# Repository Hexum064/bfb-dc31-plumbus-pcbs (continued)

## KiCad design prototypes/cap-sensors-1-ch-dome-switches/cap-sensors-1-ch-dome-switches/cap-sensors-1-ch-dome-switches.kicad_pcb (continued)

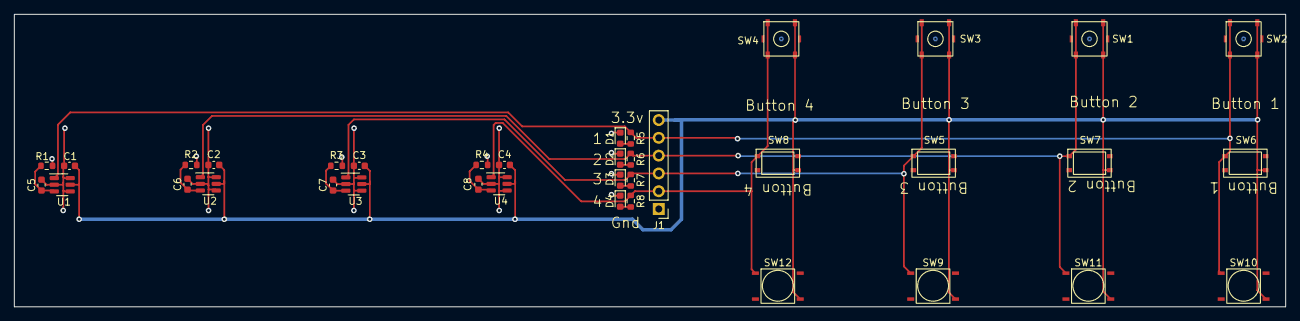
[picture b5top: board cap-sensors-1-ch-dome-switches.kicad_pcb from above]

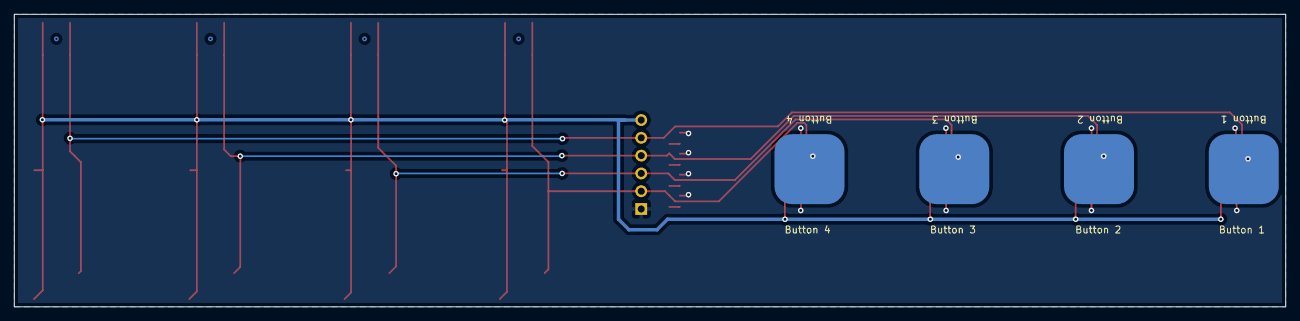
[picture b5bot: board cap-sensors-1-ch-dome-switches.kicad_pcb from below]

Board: 2 copper layers, 181.5 x 41.8 mm, 41 parts (4 on the bottom side), 18 nets.

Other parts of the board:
Button 1, Button 2, Button 3, Button 4: TP; touch_pad

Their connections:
unnamed 14: Button 1.1 (Touch_Pad); also elsewhere on the board
unnamed 15: Button 2.1 (Touch_Pad); also elsewhere on the board
unnamed 16: Button 3.1 (Touch_Pad); also elsewhere on the board
unnamed 17: Button 4.1 (Touch_Pad); also elsewhere on the board

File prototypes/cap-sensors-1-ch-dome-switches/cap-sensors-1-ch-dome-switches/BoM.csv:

Designator,Comment,Footprint,JLCPCB Part #
"C1, C2, C3, C4",100nF,Capacitor_SMD:C_0603_1608Metric,
"C5, C6, C7, C8",1pF,Capacitor_SMD:C_0603_1608Metric,
"D1, D2, D3, D4",LED,LED_SMD:LED_0603_1608Metric,
J1,Conn_01x06_Female,Connector_PinHeader_2.54mm:PinHeader_1x06_P2.54mm_Vertical,C2833331
"R1, R2, R3, R4, R5, R6, R7, R8",1K,Resistor_SMD:R_0603_1608Metric,
"SW1,SW2,SW3,SW4",Tactile Switch,dome_buttons:EVQPLDA15,C424352
"SW5,SW6,SW7",Tactile Switch,dome_buttons:GT-TC170B-H0078-L10,C2896623
"SW9,SW10,SW11,SW12",Tactile Switch,dome_buttons:TS5208A,C557590
"U1,U2,U3,U4",RH6015-C,RH6015-C,C78180

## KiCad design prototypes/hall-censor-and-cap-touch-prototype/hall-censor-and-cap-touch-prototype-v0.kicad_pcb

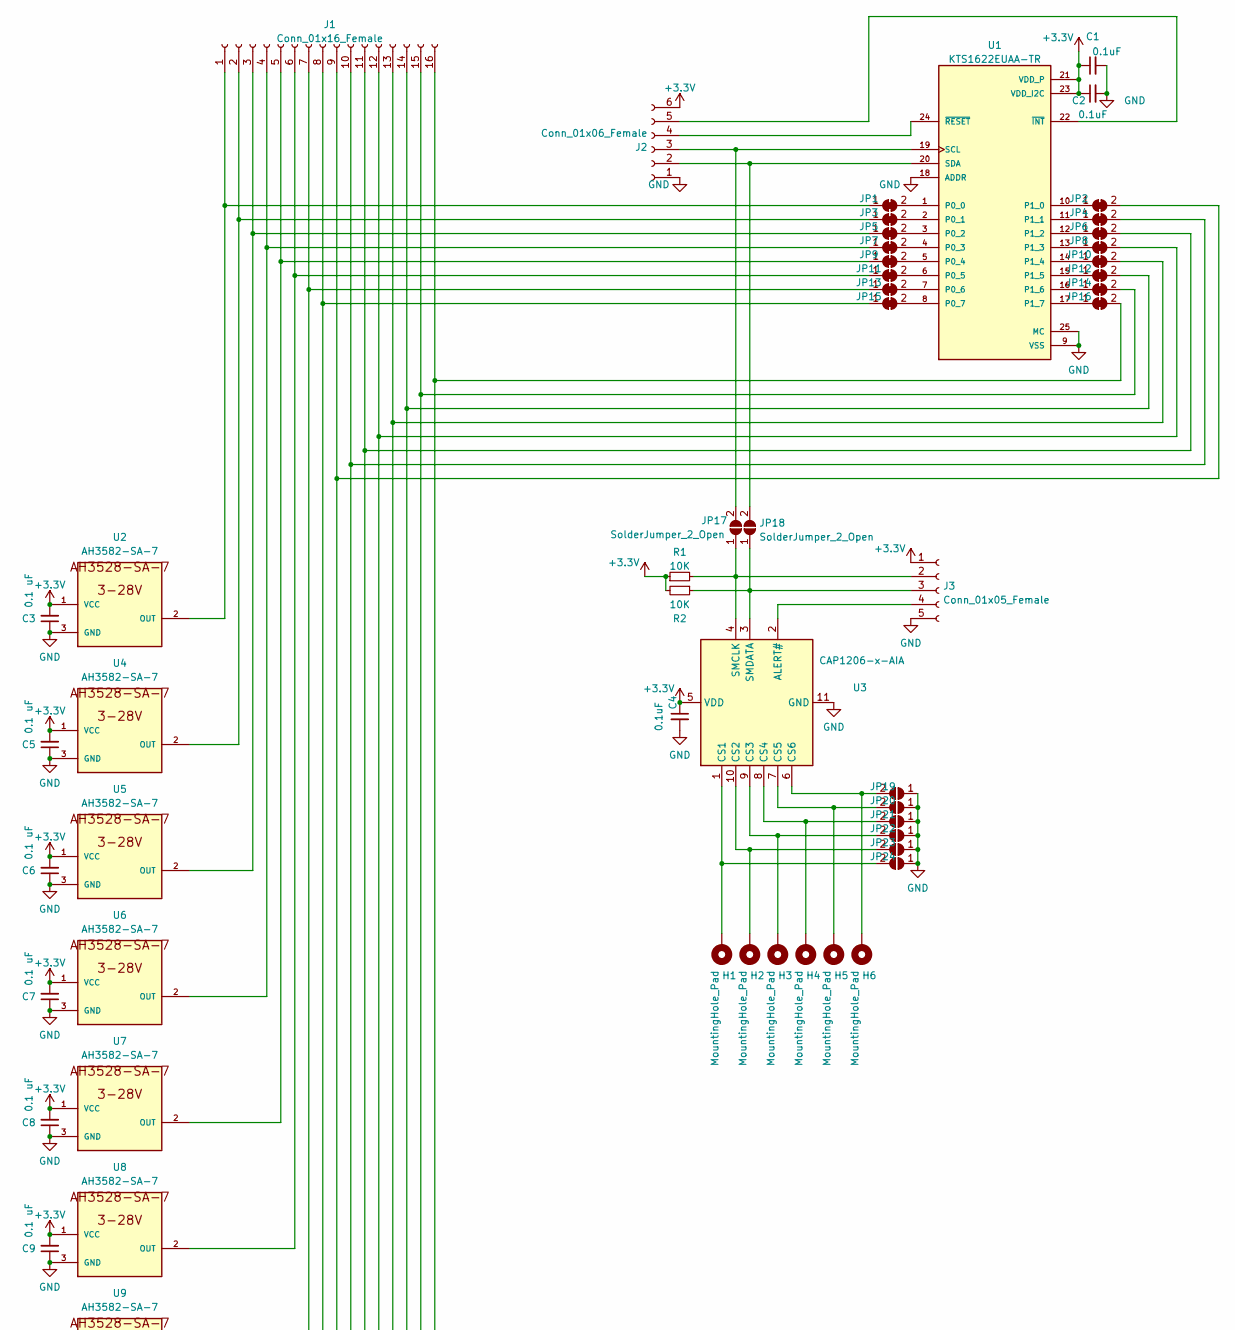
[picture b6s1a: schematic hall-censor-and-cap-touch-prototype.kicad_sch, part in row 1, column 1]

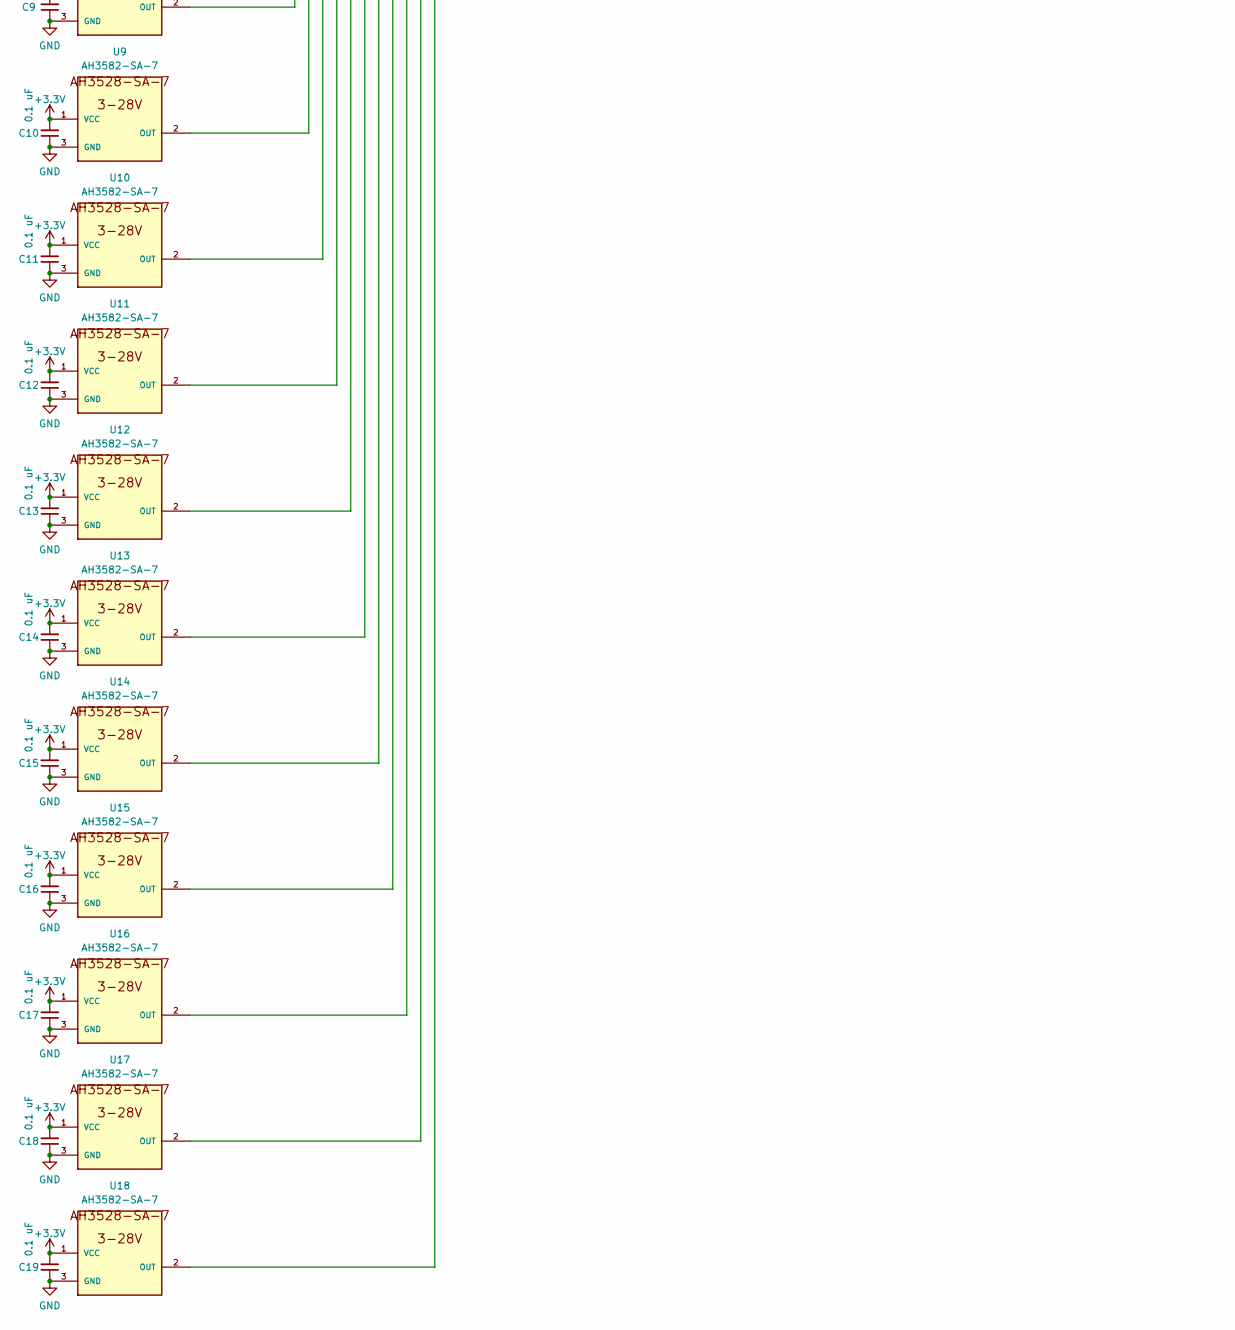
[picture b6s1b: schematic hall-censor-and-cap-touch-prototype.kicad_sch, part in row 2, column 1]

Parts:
C1, C2, C4: 0.1uF; C_0603_1608Metric
C3, C5, C6, C7, C8, C9, C10, C11, C12, C13, C14, C15, C16, C17, C18, C19: 0.1 uF; C_0603_1608Metric
H1, H2, H3, H4, H5, H6: MountingHole_Pad; TestPoint_Pad_4.0x4.0mm
J1: Conn_01x16_Female; PinHeader_1x16_P2.54mm_Vertical
J2: Conn_01x06_Female; PinHeader_1x06_P2.54mm_Vertical
J3: Conn_01x05_Female; PinHeader_1x05_P2.54mm_Vertical
JP1, JP2, JP3, JP4, JP5, JP6, JP7, JP8, JP9, JP10, JP11, JP12, JP13, JP14, JP15, JP16: SolderJumper_2_Bridged; SolderJumper-2_P1.3mm_Bridged2Bar_RoundedPad1.0x1.5mm
JP17, JP18, JP19, JP20, JP21, JP22, JP23, JP24: SolderJumper_2_Open; SolderJumper-2_P1.3mm_Open_RoundedPad1.0x1.5mm
R1, R2: 10K; R_0603_1608Metric
U1: KTS1622EUAA-TR; QFN50P400X400X80-25N; PARTREV 04d
U2, U4, U5, U6, U7, U8, U9, U10, U11, U12, U13, U14, U15, U16, U17, U18: AH3582-SA-7; SOT-23-AH3582-SA-7
U3: CAP1206-x-AIA; DFN-10-1EP_3x3mm_P0.5mm_EP1.55x2.48mm

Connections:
+3V3: C1.1, C2.1, C3.2, C4.1, C5.2, C6.2, C7.2, C8.2, C9.2, C10.2, C11.2, C12.2, C13.2, C14.2, C15.2, C16.2, C17.2, C18.2, C19.2, J2.6, J3.1, R1.1, R2.2, U1.21 (VDD_P), U1.23 (VDD_I2C), U2.1 (VCC), U3.5 (VDD), U4.1 (VCC), U5.1 (VCC), U6.1 (VCC), U7.1 (VCC), U8.1 (VCC), U9.1 (VCC), U10.1 (VCC), U11.1 (VCC), U12.1 (VCC), U13.1 (VCC), U14.1 (VCC), U15.1 (VCC), U16.1 (VCC), U17.1 (VCC), U18.1 (VCC)
GND: C1.2, C2.2, C3.1, C4.2, C5.1, C6.1, C7.1, C8.1, C9.1, C10.1, C11.1, C12.1, C13.1, C14.1, C15.1, C16.1, C17.1, C18.1, C19.1, J2.1, J3.5, JP19.1 (A), JP20.1 (A), JP21.1 (A), JP22.1 (A), JP23.1 (A), JP24.1 (A), U1.9 (VSS), U1.18 (ADDR), U1.25 (MC), U2.3 (GND), U3.11 (GND), U4.3 (GND), U5.3 (GND), U6.3 (GND), U7.3 (GND), U8.3 (GND), U9.3 (GND), U10.3 (GND), U11.3 (GND), U12.3 (GND), U13.3 (GND), U14.3 (GND), U15.3 (GND), U16.3 (GND), U17.3 (GND), U18.3 (GND)
unnamed: H1.1, JP24.2 (B), U3.1 (CS1)
unnamed: H2.1, JP23.2 (B), U3.10 (CS2)
unnamed: H3.1, JP22.2 (B), U3.9 (CS3)
unnamed: H4.1, JP21.2 (B), U3.8 (CS4)
unnamed: H5.1, JP20.2 (B), U3.7 (CS5)
unnamed: H6.1, JP19.2 (B), U3.6 (CS6)
unnamed: J1.1, JP1.1 (A), U2.2 (OUT)
unnamed: J1.2, JP3.1 (A), U4.2 (OUT)
unnamed: J1.3, JP5.1 (A), U5.2 (OUT)
unnamed: J1.4, JP7.1 (A), U6.2 (OUT)
unnamed: J1.5, JP9.1 (A), U7.2 (OUT)
unnamed: J1.6, JP11.1 (A), U8.2 (OUT)
unnamed: J1.7, JP13.1 (A), U9.2 (OUT)
unnamed: J1.8, JP15.1 (A), U10.2 (OUT)
unnamed: J1.9, JP2.2 (B), U11.2 (OUT)
unnamed: J1.10, JP4.2 (B), U12.2 (OUT)
unnamed: J1.11, JP6.2 (B), U13.2 (OUT)
unnamed: J1.12, JP8.2 (B), U14.2 (OUT)
unnamed: J1.13, JP10.2 (B), U15.2 (OUT)
unnamed: J1.14, JP12.2 (B), U16.2 (OUT)
unnamed: J1.15, JP14.2 (B), U17.2 (OUT)
unnamed: J1.16, JP16.2 (B), U18.2 (OUT)
unnamed: J2.2, JP18.2 (B), U1.20 (SDA)
unnamed: J2.3, JP17.2 (B), U1.19 (SCL)
unnamed: J2.4, U1.24 (~RESET)
unnamed: J2.5, U1.22 (~INT)
unnamed: J3.2, JP17.1 (A), R1.2, U3.4 (SMCLK)
unnamed: J3.3, JP18.1 (A), R2.1, U3.3 (SMDATA)
unnamed: J3.4, U3.2 (ALERT#)
unnamed: JP1.2 (B), U1.1 (P0_0)
unnamed: JP2.1 (A), U1.10 (P1_0)
unnamed: JP3.2 (B), U1.2 (P0_1)
unnamed: JP4.1 (A), U1.11 (P1_1)
unnamed: JP5.2 (B), U1.3 (P0_2)
unnamed: JP6.1 (A), U1.12 (P1_2)
unnamed: JP7.2 (B), U1.4 (P0_3)
unnamed: JP8.1 (A), U1.13 (P1_3)
unnamed: JP9.2 (B), U1.5 (P0_4)
unnamed: JP10.1 (A), U1.14 (P1_4)
unnamed: JP11.2 (B), U1.6 (P0_5)
unnamed: JP12.1 (A), U1.15 (P1_5)
unnamed: JP13.2 (B), U1.7 (P0_6)
unnamed: JP14.1 (A), U1.16 (P1_6)
unnamed: JP15.2 (B), U1.8 (P0_7)
unnamed: JP16.1 (A), U1.17 (P1_7)

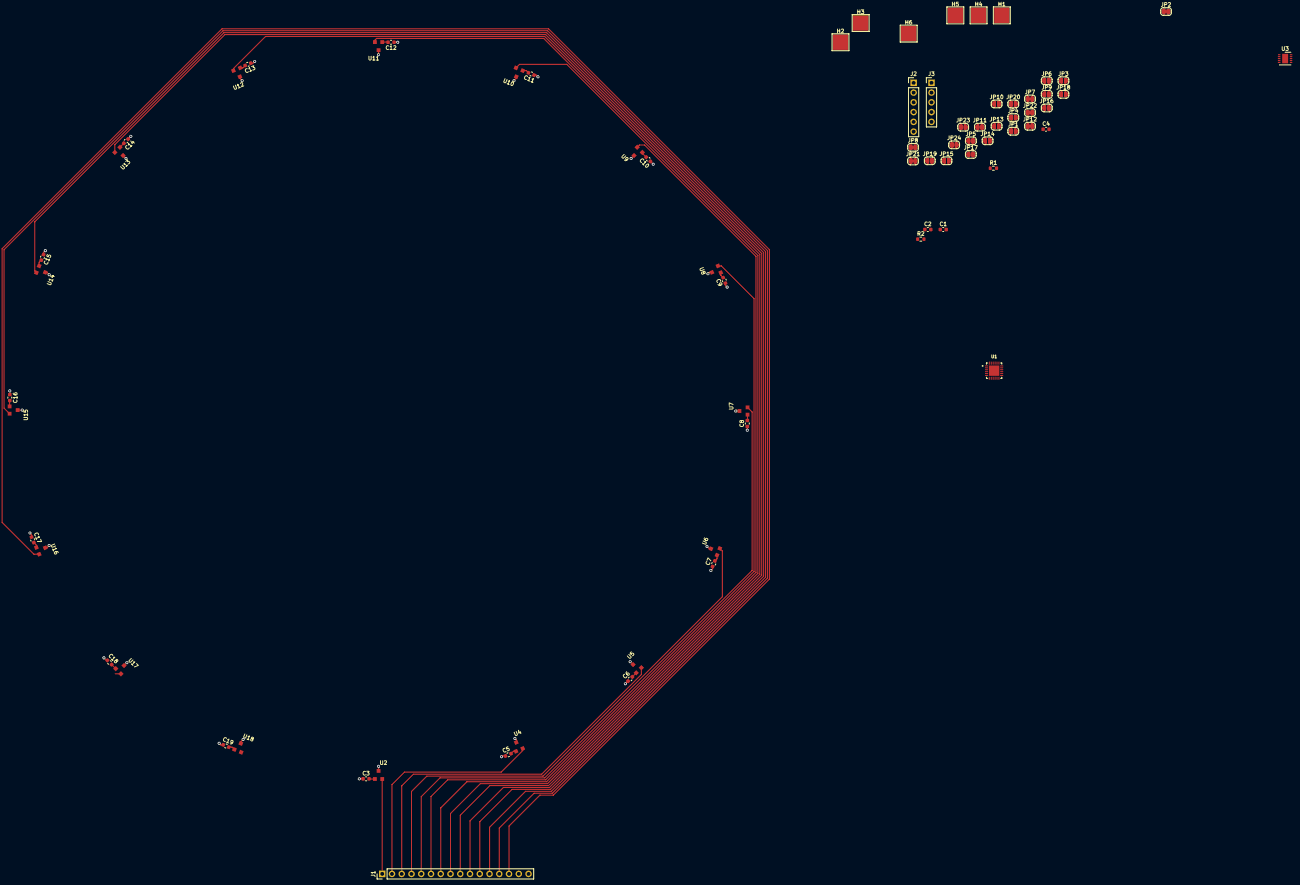
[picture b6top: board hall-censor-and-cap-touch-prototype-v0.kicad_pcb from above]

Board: 2 copper layers, 72 parts (0 on the bottom side), 47 nets.
